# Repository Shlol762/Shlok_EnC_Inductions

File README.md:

# Kratos Induction Repository

This repo contains all my required KiCAD and ROS 2 Humble packages for the Kratos Induction tasks.

## Directory Structure

### [PCB Assignments](PCB/README.md)
* **[`breakout_footprint/`](./PCB/breakout_footprint/)**: Custom symbol and footprints for I2C Multiplexer breakout board.
* **[`libs/`](./PCB/libs/)**: Custom symbols and footprint libraries for sensors (MPU6050, HC-SR04).
* **[`mcu_breakout_board/`](./PCB/mcu_breakout_board/)**: Schematic and routed PCB layout files for an ESP32 breakout board.
* **[`power_dist_box/`](./PCB/power_dist_box/)**: Placeholder directory for the power distribution board task. (Haven't completed as of Jul 7th)

### [ROS Assignments](ROS/README.md)

* **[`src/kratos_shlok`](./src/kratos_shlok)**: Node setup assignment with publisher and subscriber nodes, dealing in randomised data, using builtin message types.
* **[`src/kratos_shlok2`](./src/kratos_shlok2) & [`src/kratos_shlok_msgs`](./src/kratos_shlok_msgs)**: Node setup assignment with publisher and subscriber nodes, dealing in custom message types, using a custom message package.
* **[`src/arm_humble`](./src/arm_humble)**: Robot arm controller using FKIK principles.
* **[`src/week4_rover_control`](./src/week4_rover_control)**: Rover control node using double-Ackermann steering.

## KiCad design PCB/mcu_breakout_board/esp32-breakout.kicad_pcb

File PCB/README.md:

# PCB Tasks

This directory contains KiCad 7 schematics, layouts, and custom footprint/symbol libraries for the Kratos Induction tasks.

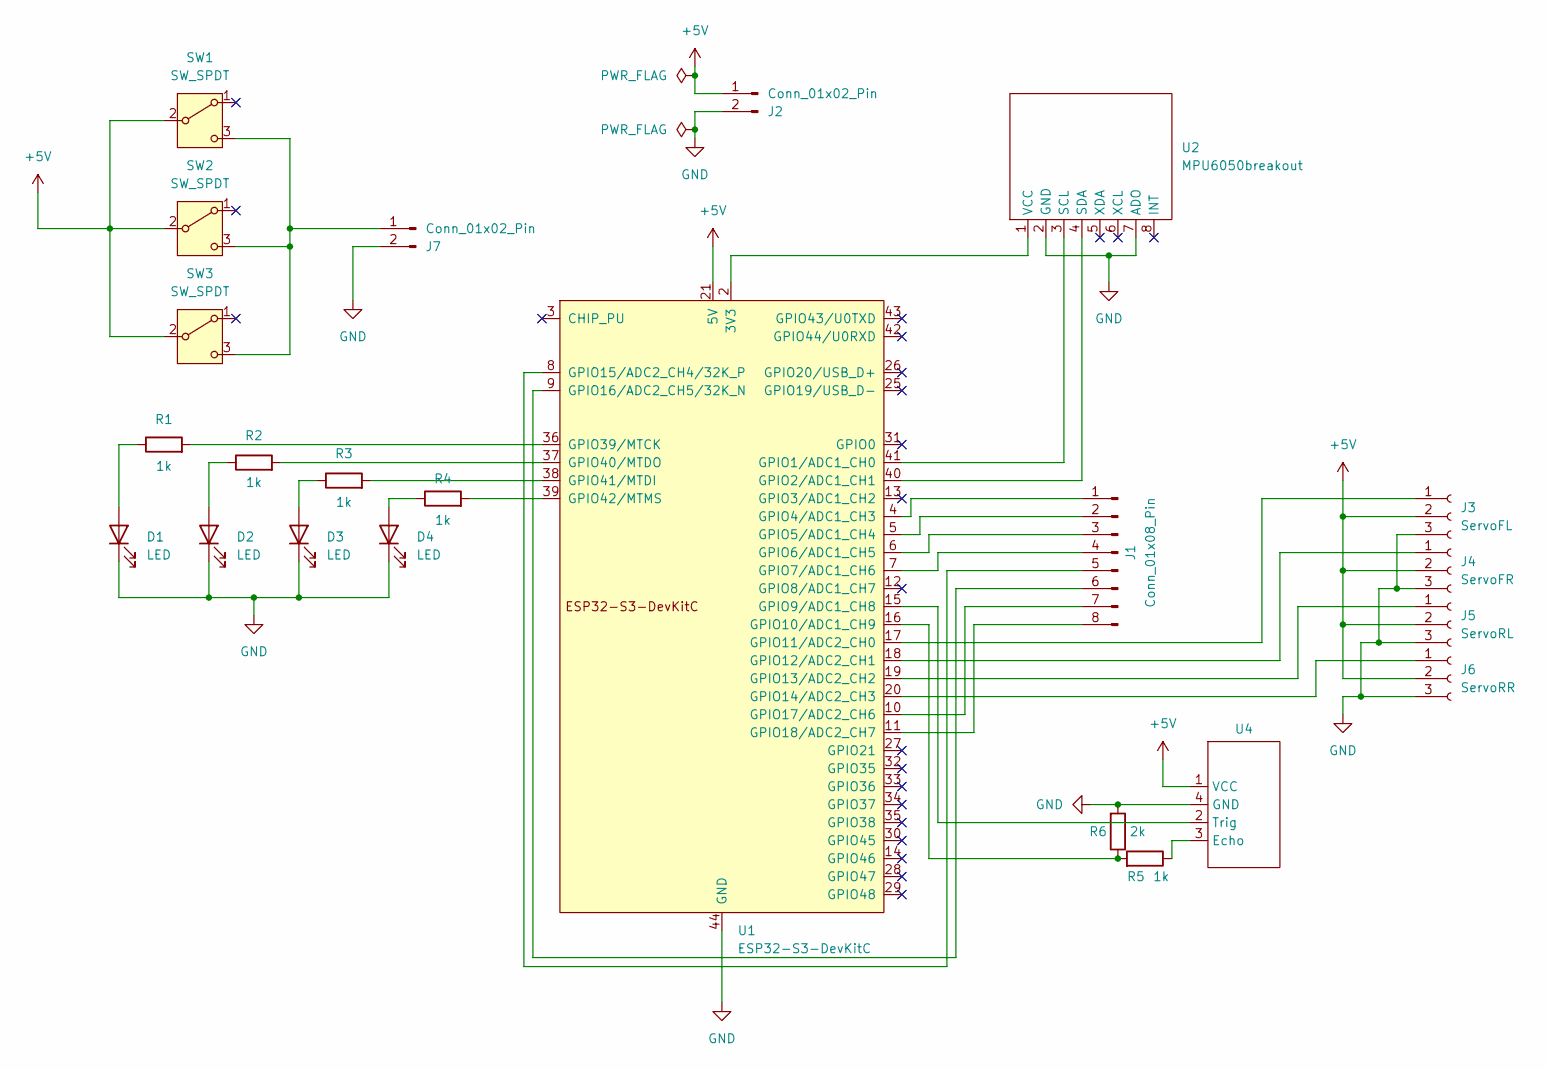
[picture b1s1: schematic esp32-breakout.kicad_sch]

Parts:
D1, D2, D3, D4: LED; LED_D3.0mm
J1: Conn_01x08_Pin; PinHeader_1x08_P2.54mm_Vertical
J2: Conn_01x02_Pin; TerminalBlock_Phoenix_MKDS-1,5-2-5.08_1x02_P5.08mm_Horizont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
J3: ServoFL; PinHeader_1x03_P2.54mm_Vertical
J4: ServoFR; PinHeader_1x03_P2.54mm_Vertical
J5: ServoRL; PinHeader_1x03_P2.54mm_Vertical
J6: ServoRR; PinHeader_1x03_P2.54mm_Vertical
J7: Conn_01x02_Pin; PinHeader_1x02_P2.54mm_Vertical
R1, R2, R3, R4, R5: 1k; R_0805_2012Metric_Pad1.20x1.40mm_HandSolder
R6: 2k; R_0805_2012Metric_Pad1.20x1.40mm_HandSolder
SW1, SW2, SW3: SW_SPDT; SW_Slide_SPDT_Straight_CK_OS102011MS2Q
U1: ESP32-S3-DevKitC
U2: MPU6050breakout
U4: hcsr04Breakout

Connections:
+5V: J2.1, J3.2, J4.2, J5.2, J6.2, SW1.2 (B), SW2.2 (B), SW3.2 (B), U1.21 (5V), U4.1 (VCC)
GND: D1.1 (K), D2.1 (K), D3.1 (K), D4.1 (K), J2.2, J3.3, J4.3, J5.3, J6.3, J7.2, R6.2, U1.22 (GND), U1.23 (GND), U1.24 (GND), U1.44 (GND), U2.2 (GND), U2.7 (ADO), U4.4 (GND)
unnamed: D1.2 (A), R1.1
unnamed: D2.2 (A), R2.1
unnamed: D3.2 (A), R3.1
unnamed: D4.2 (A), R4.1
unnamed: J1.1, U1.4 (GPIO4/ADC1_CH3)
unnamed: J1.2, U1.5 (GPIO5/ADC1_CH4)
unnamed: J1.3, U1.6 (GPIO6/ADC1_CH5)
unnamed: J1.4, U1.7 (GPIO7/ADC1_CH6)
unnamed: J1.5, U1.8 (GPIO15/ADC2_CH4/32K_P)
unnamed: J1.6, U1.9 (GPIO16/ADC2_CH5/32K_N)
unnamed: J1.7, U1.10 (GPIO17/ADC2_CH6)
unnamed: J1.8, U1.11 (GPIO18/ADC2_CH7)
unnamed: J3.1, U1.17 (GPIO11/ADC2_CH0)
unnamed: J4.1, U1.18 (GPIO12/ADC2_CH1)
unnamed: J5.1, U1.19 (GPIO13/ADC2_CH2)
unnamed: J6.1, U1.20 (GPIO14/ADC2_CH3)
unnamed: J7.1, SW1.3 (C), SW2.3 (C), SW3.3 (C)
unnamed: U1.41 (GPIO1/ADC1_CH0), U2.3 (SCL)
unnamed: U1.40 (GPIO2/ADC1_CH1), U2.4 (SDA)
unnamed: U1.15 (GPIO9/ADC1_CH8), U4.2 (Trig)
unnamed: R5.2, R6.1, U1.16 (GPIO10/ADC1_CH9)
unnamed: R1.2, U1.36 (GPIO39/MTCK)
unnamed: R2.2, U1.37 (GPIO40/MTDO)
unnamed: R3.2, U1.38 (GPIO41/MTDI)
unnamed: R4.2, U1.39 (GPIO42/MTMS)
unnamed: U1.1 (3V3), U1.2 (3V3), U2.1 (VCC)
unnamed: R5.1, U4.3 (Echo)

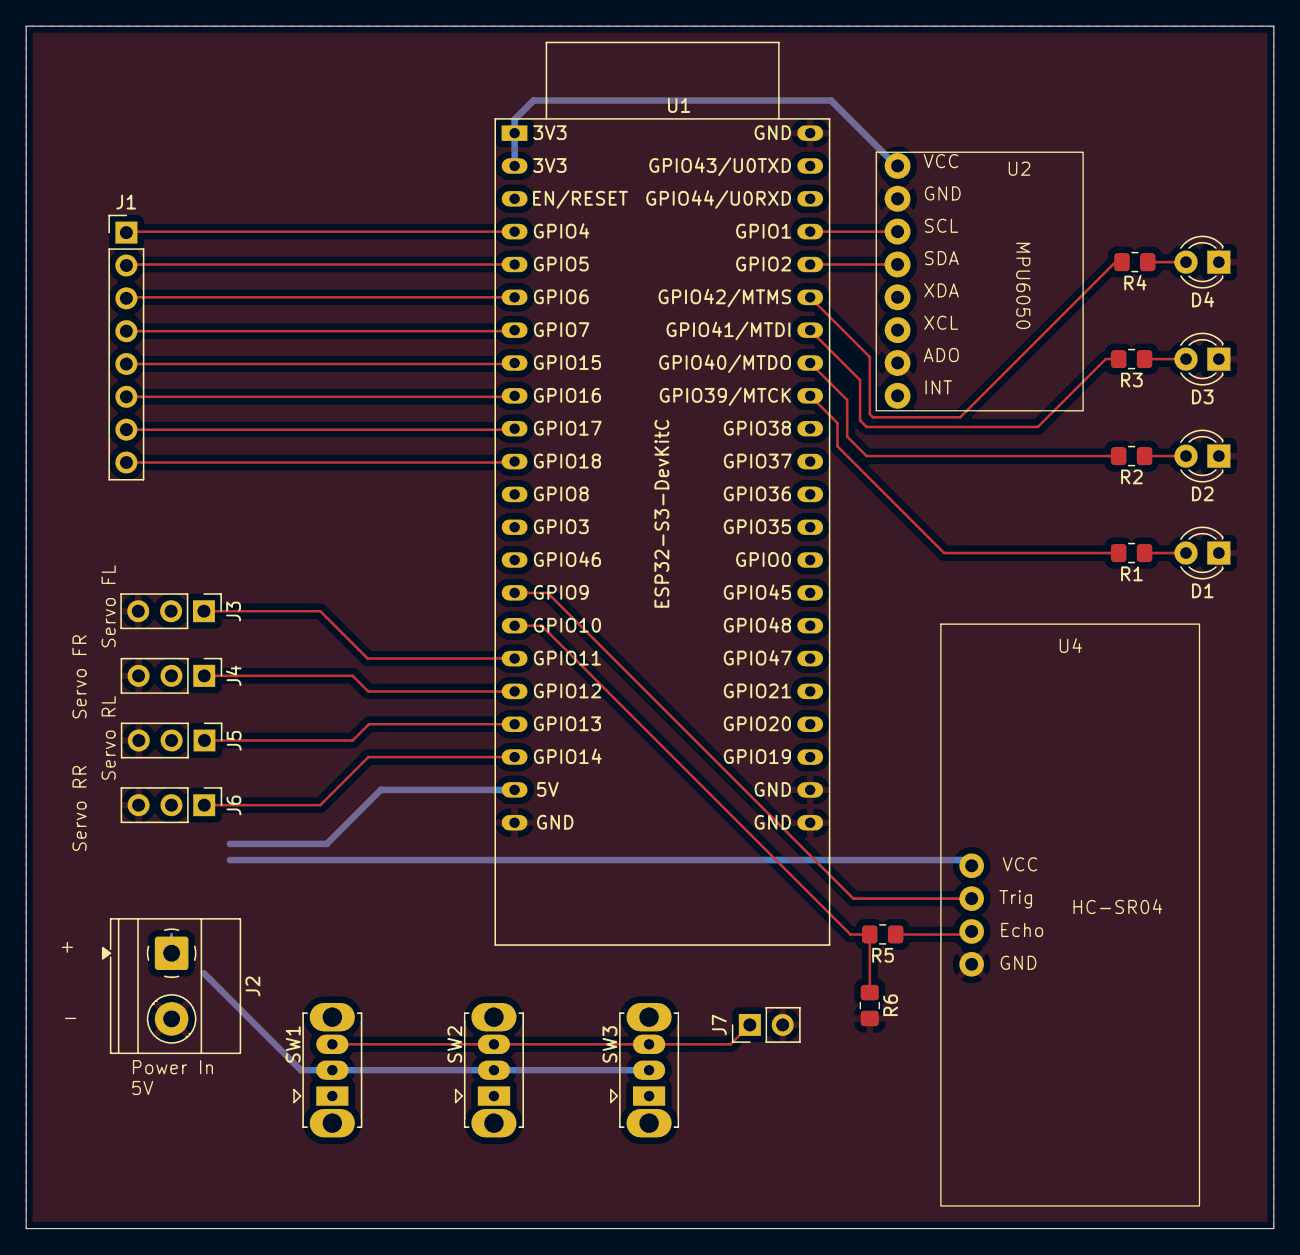
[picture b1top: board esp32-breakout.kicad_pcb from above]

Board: 2 copper layers, 96.5 x 93.0 mm, 23 parts (0 on the bottom side), 29 nets.

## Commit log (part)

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2026-06-29 Add all files for first two problem statements
